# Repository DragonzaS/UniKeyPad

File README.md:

# UniKeyPad
UniKeyPad is a 11 key macropad, with a rotary encoder and an OLED display. Uses QMK firmware!

I made as introduction for myself to PCB design, and also can be used as minimal numberpad companion for my current TKL keyboard.

## Features
- Simple, two part 3D printed case
- one Rotary Encoder for mode selection, together with 128x32 OLED display for friendly UI.
- 11 Customizable keys

## Case

Together it fits using two 3D printed parts, that are kept together with four M3 screws and heatset inserts.
(Angled stand coming soon, to have same angle as my main keyboard)

All together

Case only

Made with OnShape.

(To the reviewer: I added a simplified CAD file, without the switches, the full size one is very big!)
## PCB

Made in Kicad (my first time!). Included also 3D models that I used (they are from GrabCad), it was quite a pain to get them working.

Schematic

PCB

Also tried using Ground plane and thicker traces for 5V to OLED for stability.

## Firmware

For now QMK only, might do a KMK version.

OLED is not yet implemented, everything else should work.
Basic functionality tested with a Raspberry Pico and a dupont cable :)
Works!

## Bill of Materials
Hopefully everything that I used:

- 11x Cherry MX Switches
- 11x DSA Keycaps
- 11x 1N4148 Diodes
- 4x M3x5x4 Heatset inserts
- 4x M3x12mm SHCS Bolts
- 1x 0.91" 128x32 OLED Display
- 1x EC11 Rotary Encoder
- 1x XIAO RP2040
- 1x Case, two 3D printed parts (I can print them myself)

## Extra
I enjoyed making it!

Possible thanks to HackClub!

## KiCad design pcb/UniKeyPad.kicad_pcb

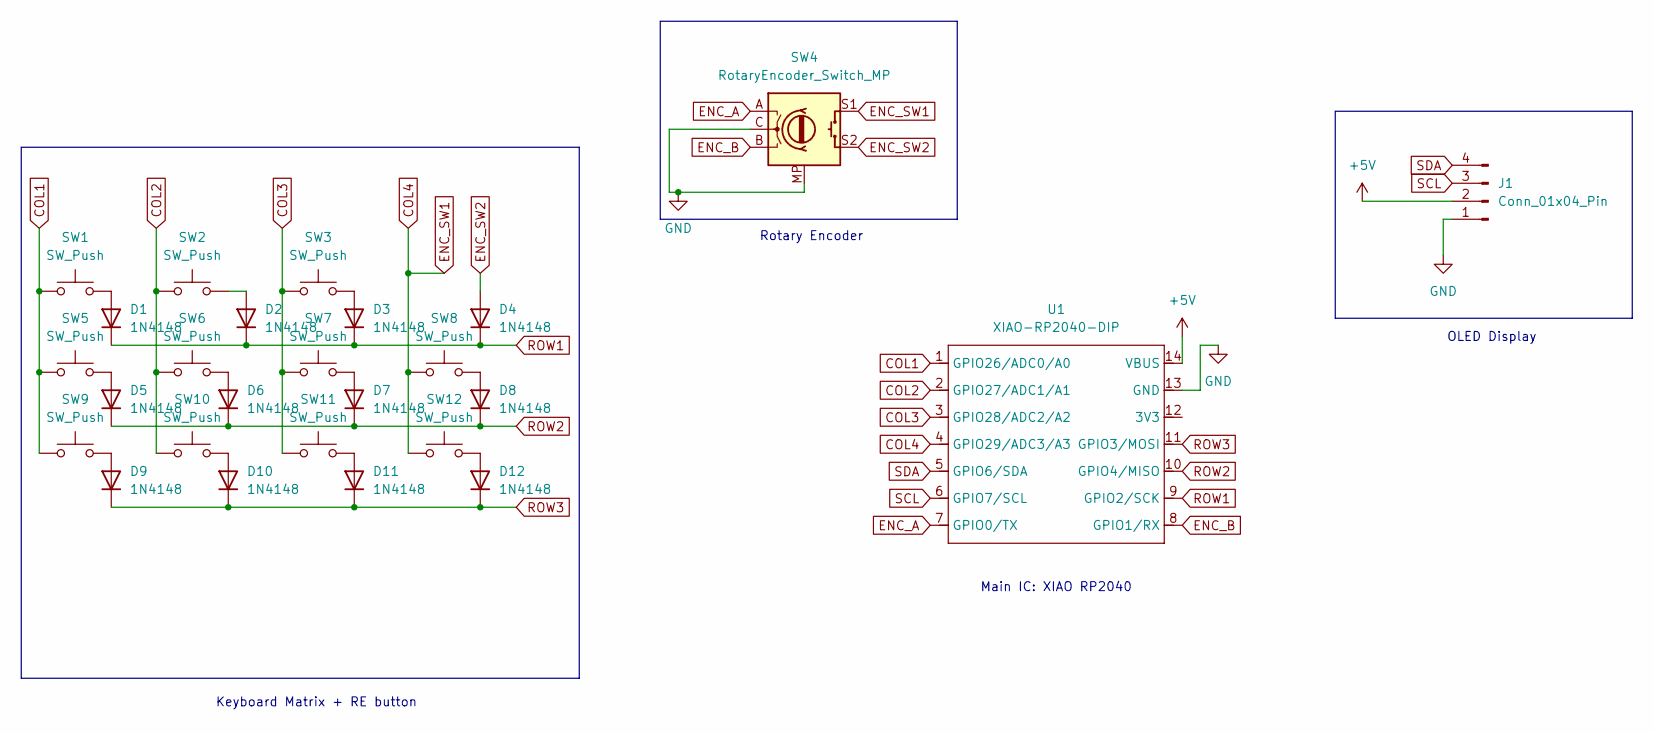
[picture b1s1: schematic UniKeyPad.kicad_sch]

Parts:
D1, D2, D3, D4, D5, D6, D7, D8, D9, D10, D11, D12: 1N4148; D_DO-35_SOD27_P7.62mm_Horizontal
J1: Conn_01x04_Pin; SSD1306-0.91-OLED-4pin-128x32
SW1, SW2, SW3, SW5, SW6, SW7, SW8, SW9, SW10, SW11, SW12: SW_Push; SW_Cherry_MX_1.00u_PCB_3D
SW4: RotaryEncoder_Switch_MP; RotaryEncoder_Alps_EC11E-Switch_Vertical_H20mm
U1: XIAO-RP2040-DIP

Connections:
+5V: J1.2, U1.14 (VBUS)
COL1: SW1.1, SW5.1, SW9.1, U1.1 (GPIO26/ADC0/A0)
COL2: SW2.1, SW6.1, SW10.1, U1.2 (GPIO27/ADC1/A1)
COL3: SW3.1, SW7.1, SW11.1, U1.3 (GPIO28/ADC2/A2)
COL4: SW4.S1, SW8.1, SW12.1, U1.4 (GPIO29/ADC3/A3)
ENC_A: SW4.A, U1.7 (GPIO0/TX)
ENC_B: SW4.B, U1.8 (GPIO1/RX)
ENC_SW2: D4.2 (A), SW4.S2
GND: J1.1, SW4.C, SW4.MP, U1.13 (GND)
unnamed: D1.2 (A), SW1.2
unnamed: D2.2 (A), SW2.2
unnamed: D3.2 (A), SW3.2
unnamed: D5.2 (A), SW5.2
unnamed: D6.2 (A), SW6.2
unnamed: D7.2 (A), SW7.2
unnamed: D8.2 (A), SW8.2
unnamed: D9.2 (A), SW9.2
unnamed: D10.2 (A), SW10.2
unnamed: D11.2 (A), SW11.2
unnamed: D12.2 (A), SW12.2
ROW1: D1.1 (K), D2.1 (K), D3.1 (K), D4.1 (K), U1.9 (GPIO2/SCK)
ROW2: D5.1 (K), D6.1 (K), D7.1 (K), D8.1 (K), U1.10 (GPIO4/MISO)
ROW3: D9.1 (K), D10.1 (K), D11.1 (K), D12.1 (K), U1.11 (GPIO3/MOSI)
SCL: J1.3, U1.6 (GPIO7/SCL)
SDA: J1.4, U1.5 (GPIO6/SDA)

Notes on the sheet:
Keyboard Matrix + RE button
Rotary Encoder
OLED Display
Main IC: XIAO RP2040

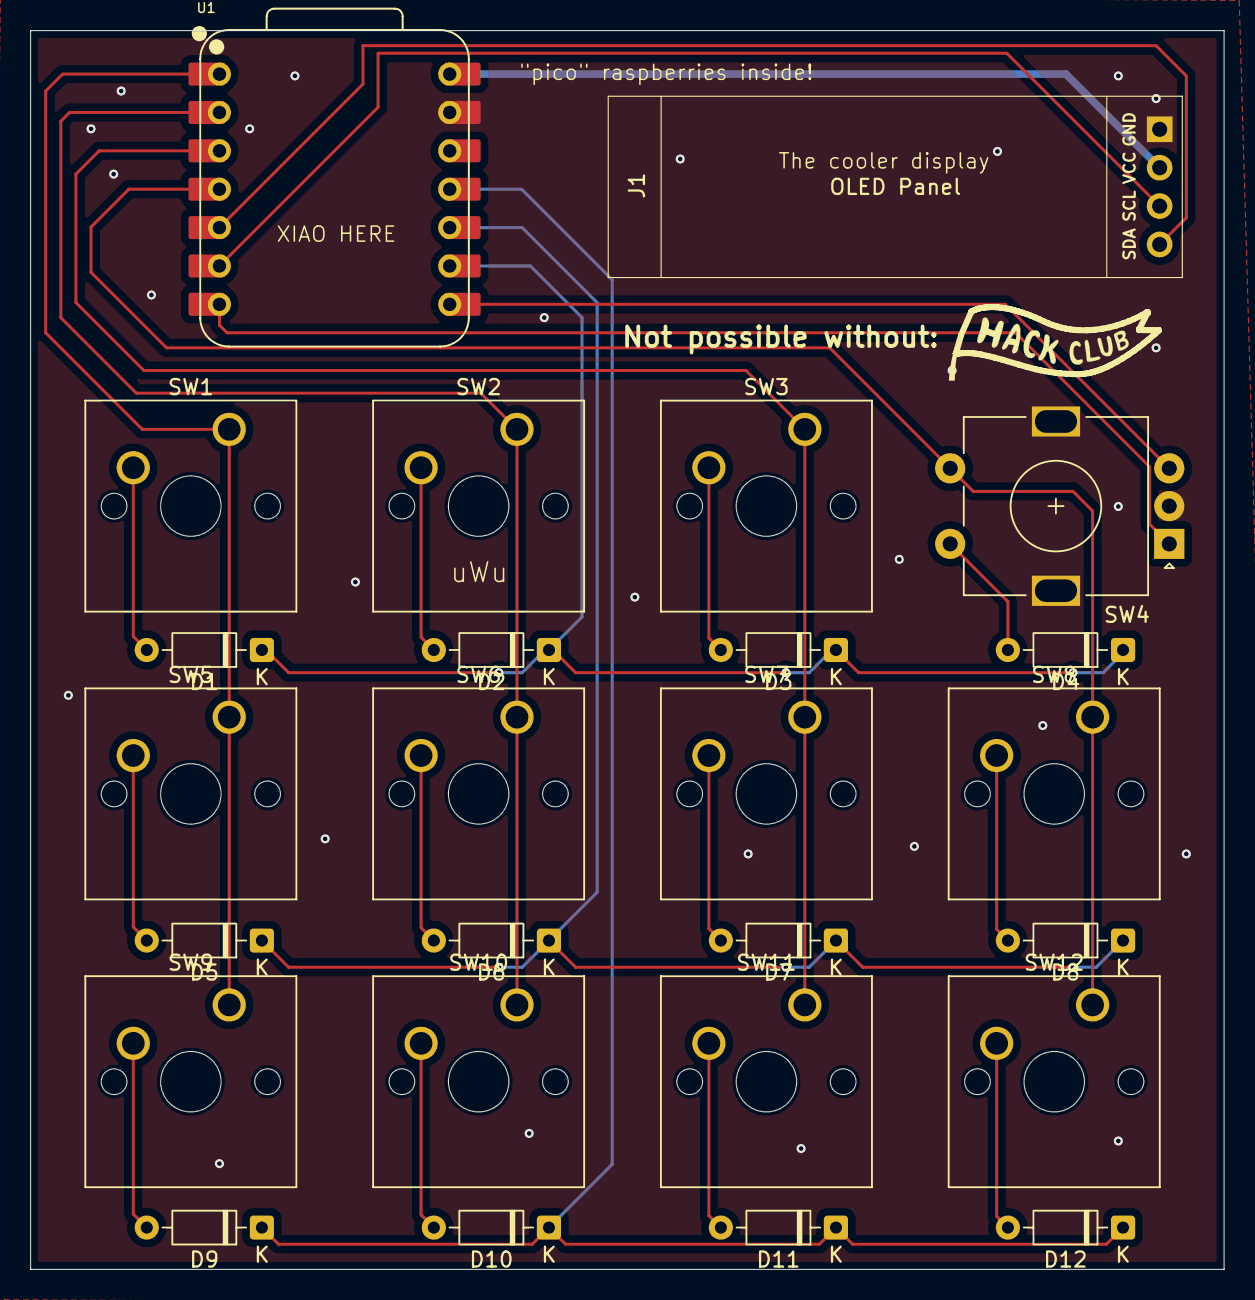
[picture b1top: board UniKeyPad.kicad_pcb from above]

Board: 2 copper layers, 79.0 x 82.0 mm, 26 parts (0 on the bottom side), 25 nets.

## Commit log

2025-07-18 Adding backup of Kicad Project
2025-07-18 hopefully everything needed is included in the Kicad zip file
2025-07-18 final? version of test zip
2025-07-18 Create cad
2025-07-18 remove mistaken files
2025-07-18 Start new folder
2025-07-18 Add files via upload
    Files from KiCad
2025-07-19 Final? PCB folder contents, kicad
2025-07-19 forgot these lol
2025-07-19 Added pictures
2025-07-19 Updated README.md with images
2025-07-19 Finalizing everything needed, before starting the QMK journey
2025-07-19 Added warning about the CAD file
2025-07-19 Added CASE screenshot
2025-07-19 Typos fixed
2025-07-19 Added QMK firmware source code and built .uf2 image
2025-11-28 Modify one image
    Bad formatting of the image
2025-11-28 another try
2025-11-28 Fix PCB image source in README
    Updated PCB image source attribute in README.
